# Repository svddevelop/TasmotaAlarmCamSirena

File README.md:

# Tasmota Alarm Camera and Sirena Control

This is a budget control unit that allows connecting a siren and an IPC camera using the DI contact.  
Power supply: 5V – 12V.  
Connection to an external siren with voltage level matching the power supply.  
Camera control connection to the DI signal at 3.3V level.

### Tasmota Configuration

The configuration includes the following elements:

- **Relay1** — enables monitoring of the sensor.  
  Used to activate tracking of the sensor signal (e.g., Reed contact).  
  Can be activated via the device control panel, through the web interface with the request  
  `http://<device_ip>/cm?cmnd=power1%201` (to turn on) and  
  `http://<device_ip>/cm?cmnd=power1%200` (to turn off),  
  or by sending an MQTT message to the topic  
  `cmnd/tasmota_<DeviceID>/POWER1` with payload `ON` or `OFF`.

- **Relay2** — forced siren activation.  
  If a siren is used, its activation can be triggered programmatically via the device control panel,  
  through the web interface with the request  
  `http://<device_ip>/cm?cmnd=power2%201` (to turn on) and  
  `http://<device_ip>/cm?cmnd=power2%200` (to turn off),  
  or by sending an MQTT message to the topic  
  `cmnd/tasmota_<DeviceID>/POWER2` with payload `ON` or `OFF`.  
  If a camera is used, the recording trigger signal will be sent automatically.

- **Switch3** — shows the current state of the sensor.  
  Can be checked via the web interface with the request  
  `http://<device_ip>/cm?cmnd=status%2010`,  
  or through MQTT by sending the message `10` to the topic  
  `cmnd/tasmota_<DeviceID>/Status`.

`<device_ip>` — the unique IP address of the device in your network.  
`<DeviceID>` — the unique identifier of the device.
### Curcuit

[see](circuit/kicad/Esp8266-DomoticzAlarm-2B/README.md)

### Plugin for Domoticz

[see](scripts/Domoticz/plugins/TasmotaMQTTAlarmCtrl/README.md)

---
---

More description you can see at [this site](https://smartthings.cloudns.org/).

[The device installation](https://smartthings.cloudns.org/page/tacs/)

[The case for the device](https://www.thingiverse.com/thing:7336493)

[The case for the reed-contact](https://www.thingiverse.com/thing:7336538)

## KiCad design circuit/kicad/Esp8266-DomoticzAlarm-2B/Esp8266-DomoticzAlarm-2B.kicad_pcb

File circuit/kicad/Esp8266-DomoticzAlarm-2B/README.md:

# Circuit

### Shematic

[Curcuit](Esp8266-DomoticzAlarm-2B.pdf)

### Board

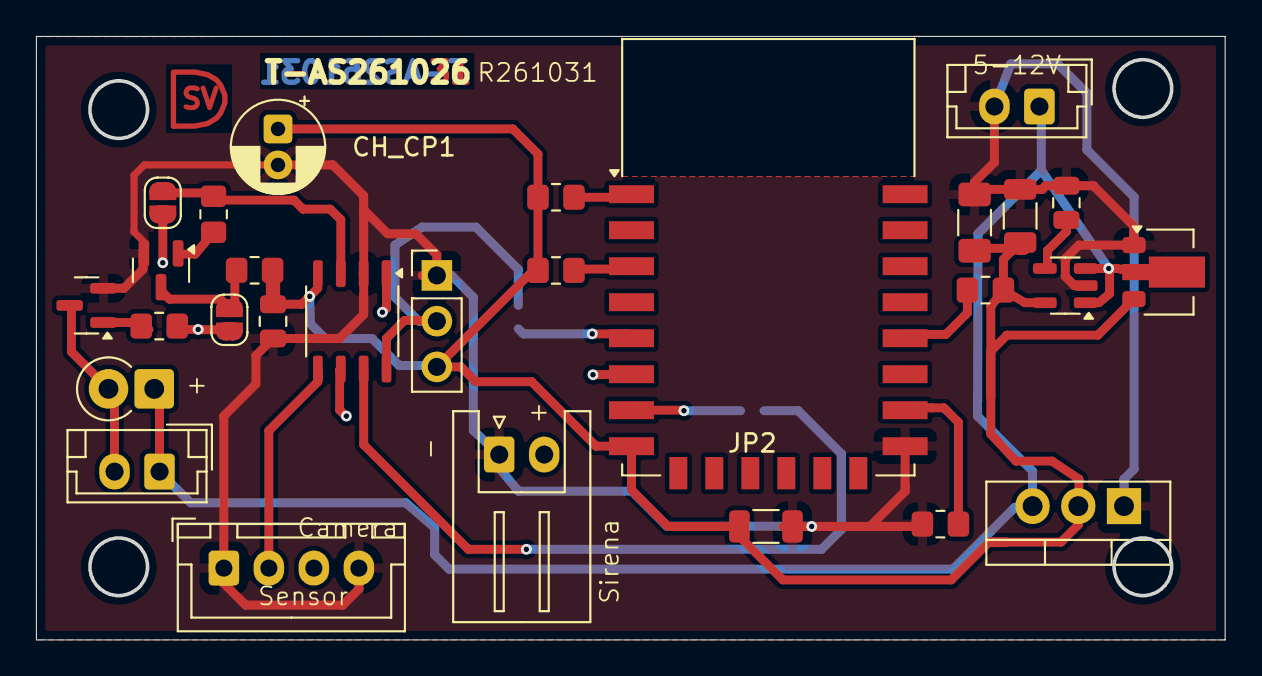
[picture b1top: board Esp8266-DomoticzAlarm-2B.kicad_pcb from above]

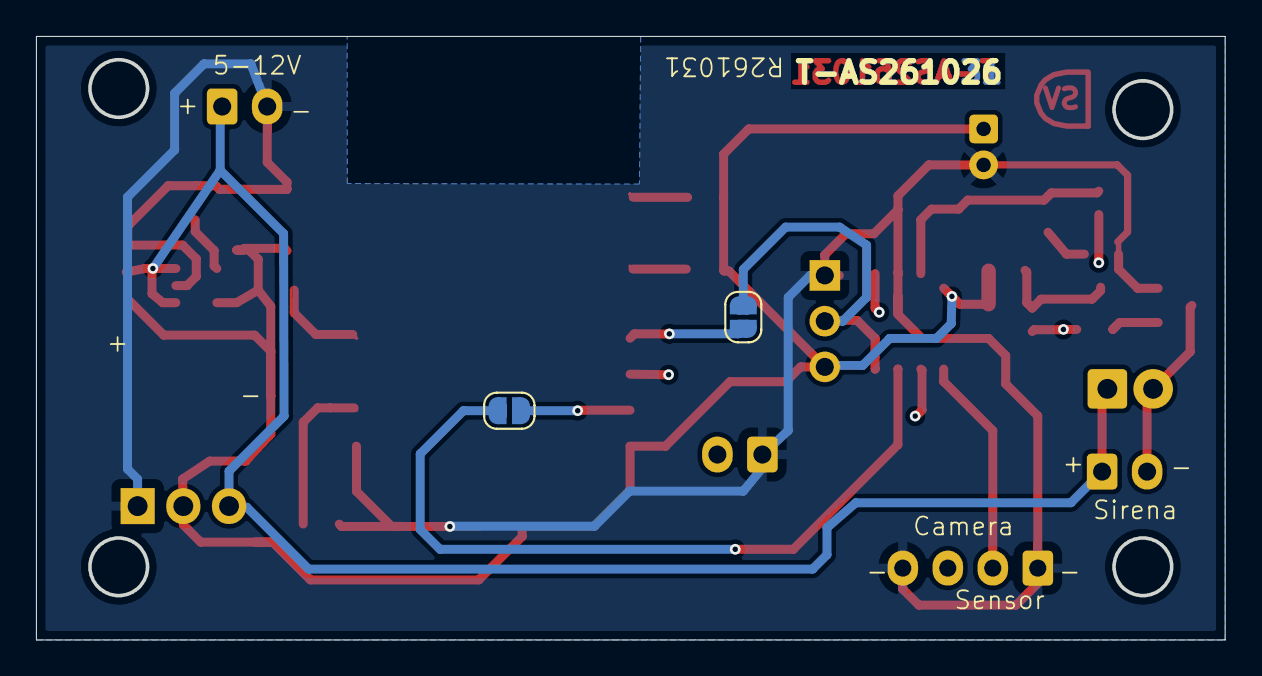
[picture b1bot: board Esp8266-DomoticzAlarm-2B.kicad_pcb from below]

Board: 4 copper layers, 66.0 x 33.5 mm, 30 parts (2 on the bottom side), 21 nets.

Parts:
CH_C1: 100nF; C_0805_2012Metric
CH_C2, CH_C4: 100nF; C_1206_3216Metric
CH_C3: 4,7µF; C_1206_3216Metric_Pad1.33x1.80mm_HandSolder
CH_C5: 470nF; C_0805_2012Metric
CH_CP1: C_Polarized; CP_Radial_D5.0mm_P2.00mm
CH_J7: ALARM_IN; JST_XH_B4B-XH-A_1x04_P2.50mm_Vertical
CH_J8: CH_ALARM_OUT; JST_EH_B2B-EH-A_1x02_P2.50mm_Vertical
CH_J10: CH_12V; JST_EH_B2B-EH-A_1x02_P2.50mm_Vertical
D1: 1N4001; D_DO-41_SOD81_P2.54mm_Vertical_KathodeUp
J2a1: Conn_01x02; JST_XH_S2B-XH-A_1x02_P2.50mm_Horizontal
JP1, JP2, JP3, JP4: Jumper_2_Bridged; SolderJumper-2_P1.3mm_Open_RoundedPad1.0x1.5mm
Q1, Q2: BC817; SOT-23
R1, R8: 100; R_0805_2012Metric_Pad1.20x1.40mm_HandSolder
R2, R3, R4, R5, R10: 10k; R_0805_2012Metric_Pad1.20x1.40mm_HandSolder
U1: CH32V003JxMx; JEITA_SOIC-8_3.9x4.9mm_P1.27mm
U2: ESP-12E
U3: HT7333; SOT-89-3
U4: MIC5219-3.3YM5; SOT-23-5
U5: LD1117V33; TO-220-3_Vertical
ch_J3: CH_PROG; PinHeader_1x03_P2.54mm_Vertical

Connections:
A1-: CH_J8.2, D1.2 (A), Q2.3 (C)
ALARMFROMESP: JP4.1 (A), U2.5 (GPIO14)
ALARM_CAM_DI: CH_J7.3, U1.1 (PD6/PA1)
B1+: CH_J8.1, CH_J10.1, D1.1 (K), U3.2 (VIN), U4.1 (IN), U4.3 (EN), U5.3 (VI)
CH_A2: JP1.1 (A), R8.2, U1.3 (PA2)
CH_ALARM_BREAKE_A: U1.6 (PC2), U2.6 (GPIO12)
CH_ALARM_IN: CH_J7.2, J2a1.2, U1.5 (PC1)
CH_C4: JP2.2 (B), U1.7 (PC4)
CH_D1D4D4: JP4.2 (B), U1.8 (PD1/PD4/PD5), ch_J3.2
CH_GND: CH_C1.2, CH_C2.1, CH_C3.1, CH_C4.2, CH_C5.1, CH_CP1.2, CH_J7.1, CH_J7.4, CH_J10.2, J2a1.1, Q1.2 (E), Q2.2 (E), R3.1, U1.2 (VSS), U2.15 (GND), U3.1 (GND), U4.2 (GND), U5.1 (GND), ch_J3.1
CH_VDD: CH_C1.1, CH_C2.2, CH_C3.2, CH_C4.1, CH_CP1.1, R2.2, R4.2, R5.2, R10.2, U1.4 (VDD), U2.8 (VCC), U3.3 (VOUT), U4.5 (OUT), U5.2 (VO), ch_J3.3
unnamed: JP1.2 (B), JP3.1 (A), R1.2
unnamed: JP3.2 (B), Q1.3 (C), R10.1
unnamed: Q1.1 (B), R8.1
unnamed: Q2.1 (B), R1.1
unnamed: R5.1, U2.3 (EN)
unnamed: R4.1, U2.18 (GPIO0)
unnamed: R3.2, U2.16 (GPIO15)
unnamed: R2.1, U2.1 (~RST)
unnamed: CH_C5.2, U4.4 (BP)
SWITCH_ALARMSTATUS: JP2.1 (A), U2.7 (GPIO13)

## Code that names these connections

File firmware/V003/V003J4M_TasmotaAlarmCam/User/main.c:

//  This µC have 3 inputs signals:
//    PC1 - Alarm Input
//    PC2 - Alarm break (from µC)
//    PC3 - Alarm break (external button)
//
// ... and one output: 
//    PA1 - Alaram output (Piezo-buzzer Sirena)
//
// The external µC set the alarm-signal on "Alarm Input".
// The the alarm doesn't breaked, switched between 2 tones(phases).
// The alarm could be breaked from external µC ("Alarm break (from µC)" must be BREAK_ACTIVE)
//   or from the externam button "Alarm break (external button)" (it must be reise from BREAK_INACTIVE to BREAK_ACTIVE)

//
//  251208-1955 it works
// 

//  251225 - it was changed for tasmota camera1
//

// !!! whan need to append:
//   1) PIN_ALARM_BREAK_B need to change as output for tasmota on pin io14/io3 (type "switch")
//        it could be see the status 


// KiCAD project Z:\WI\pcb\ESP8266\Esp8266-DomoticzAlarm-2\Esp8266-DomoticzAlarm-2A.kicad_pro\Esp8266-DomoticzAlarm-2B

// ===================================================================================
// Libraries, Definitions and Macros
// ===================================================================================
#include "system.h"                               // system functions
#include <gpio.h>                                 // GPIO functions

#include "SYS/millis.h"
//
//        ---------------
//    1 -| PD6       PD5 |- 8
//    2 -| GND       PC4 |- 7
//    3 -| PA2       PC2 |- 6
//    4 -| VCC       PC1 |- 5
//        ---------------
//        ----------------------------------
//    1 -| PIN_ALARM_PS2  WDIO              |- 8
//    2 -| GND            PIN_ALARM_PSL     |- 7
//  * 3 -| PIN_ALARM_PS   PIN_ALARM_BREAK_A |- 6
//    4 -| VCC            PIN_ALARM_INPUT   |- 5 *
//        ----------------------------------
//

//#define PIN_LED   PC0        
#define PIN_WDIO            PD5
#define PIN_ESPALARM        PIN_WDIO  //[I] programmable alarm from ESP. For include these code-snipped need to define #ALARMFROMESP 
#define ALARMFROMESP

#define PIN_ALARM_PS        PA2     // (O)Alarm signal to the Piezo-Buzzer
#define PIN_ALARM_PS2       PD6     // (O)Alarm signal to the Piezo-Buzzer
#define PIN_ALARM_INPUT     PC1     // (I) Alarm input (reed)                     
#define PIN_ALARM_BREAK_A   PC2     // (I) the reaction                          
#define PIN_ALARM_PSL       PC4     // (O) Alarm for ESP

#define BREAK_ACTIVE        (1)
#define BREAK_INACTIVE      (0)

#define ALARM_PULSE_ON      (1)     // the Piezo-buzzer activated
#define ALARM_PULSE_OFF     (0)     // the Piezo-buzzer deactivated

#define ALARM_ON            (1)
#define ALARM_OFF           (0)

#define ALARM_PERIOD_ON     (1000)  // Period in ms, when the Piezo-buzzer is active
#define ALARM_PERIOD_OFF    (500)   // Period in ms, when the Piezo-buzzer is inactive




static struct{

  uint8_t breaked : 1;          //The breaked == BREAK_ACTIVE means that does not need  to do something for alarm
  uint8_t pulse_on: 1;          //When is alarm active, can be swithc between two phases : ALARM_PERIOD_ON and ALARM_PERIOD_OFF
  uint8_t last_break_a: 1;      //It shows that the break active from external µC and does not need to switch alarm
  uint8_t last_break_b: 1;
  uint8_t last_alarm: 1;

} g_status;

#define ALARM_PS(x)         PIN_write(PIN_ALARM_PS, x);PIN_write(PIN_ALARM_PS2, x)


// ===================================================================================
// Main Function
// ===================================================================================
int main(void) {

  STK_init();
  HSI_enable();


  // Setup
  PIN_output(PIN_ALARM_PS);                         // Alarm signal to the Piezo-Buzzer
  PIN_output(PIN_ALARM_PS2);                        // Alarm signal to the Piezo-Buzzer
  PIN_output(PIN_ALARM_PSL);                        // Alarm signal to the ESP
  PIN_write(PIN_ALARM_PS, ALARM_PERIOD_OFF);
  PIN_write(PIN_ALARM_PS2, ALARM_PERIOD_OFF);
  PIN_write(PIN_ALARM_PSL, ALARM_PERIOD_OFF);

  PIN_input_PU(PIN_ALARM_INPUT);                    // Alarm activation on reise from ALARM_OFF to ALARM_ON
  PIN_input(PIN_ALARM_BREAK_A);                  // Stop alarm. It going from µC
  //PIN_input(PIN_ALARM_BREAK_B);                  // With pull-up.  Stop alarm from the external button

  #ifdef ALARMFROMESP
  PIN_input_PU(PIN_ESPALARM);
  #endif


  
  //ALARM_PS(ALARM_PULSE_OFF);   
  PIN_write(PIN_ALARM_PS, ALARM_PULSE_OFF);
  PIN_write(PIN_ALARM_PS2, ALARM_PULSE_OFF);             

  g_status.breaked    =   BREAK_INACTIVE;
  g_status.pulse_on   =   ALARM_PULSE_ON;
  g_status.last_alarm =   ALARM_OFF;

  // Loop
  while(1) {

    uint8_t pin;



    //
    pin = PIN_read(PIN_ALARM_INPUT);
    PIN_write(PIN_ALARM_PSL, pin); 
    if ((pin == ALARM_ON) & (g_status.last_alarm == ALARM_OFF))
        g_status.last_alarm = ALARM_ON;

    //if (pin == ALARM_OFF)
    //    g_status.last_alarm = ALARM_OFF;

    //*/    

    //
    pin = PIN_read(PIN_ALARM_BREAK_A);

    if (( pin == BREAK_ACTIVE) )//& ( g_status.last_break_a == BREAK_INACTIVE))
    {

      g_status.breaked = BREAK_ACTIVE; 
      g_status.last_break_b = BREAK_INACTIVE;
    }
    else 
      g_status.breaked = BREAK_INACTIVE;

    g_status.last_break_a = pin;
    //*/


    // check for the break from the stop-alarm button
    pin = BREAK_INACTIVE;
    g_status.last_break_b = pin;
    //*
    #ifdef ALARMFROMESP
    pin = PIN_read(PIN_ESPALARM);
    if (( pin == ALARM_ON))// & ( g_status.last_break_b == BREAK_INACTIVE))  
    {
      g_status.breaked    = BREAK_INACTIVE; 
      g_status.last_alarm = ALARM_ON;
    }
    //g_status.last_break_b = pin;
    #endif
    //*/

    // switch alarm to OFF if any break is active
    if (g_status.breaked == BREAK_ACTIVE){

        //ALARM_PS(ALARM_PULSE_OFF);
        PIN_write(PIN_ALARM_PS, ALARM_PULSE_OFF);
        PIN_write(PIN_ALARM_PS2, ALARM_PULSE_OFF);             
        //PIN_write(PIN_ALARM_PSL, ALARM_PULSE_OFF);             
        g_status.last_alarm = ALARM_OFF;
    }
    //*/

    

    //
    //pin = ALARM_ON;
    //g_status.last_alarm = ALARM_OFF;

    if (g_status.last_alarm == ALARM_ON) {  

                   
      if (g_status.breaked == BREAK_INACTIVE){

        if (g_status.pulse_on == ALARM_PULSE_ON){

          //ALARM_PS(ALARM_PULSE_ON);
          PIN_write(PIN_ALARM_PS, ALARM_PULSE_ON);
          PIN_write(PIN_ALARM_PS2, ALARM_PULSE_ON);             
          g_status.pulse_on = ALARM_PULSE_OFF;
          DLY_ms(ALARM_PERIOD_ON);

        }
        else { //if (g_status.pulse_on == ALARM_PULSE_ON)

          //ALARM_PS(ALARM_PULSE_OFF);
          PIN_write(PIN_ALARM_PS, ALARM_PULSE_OFF);
          PIN_write(PIN_ALARM_PS2, ALARM_PULSE_OFF);             
          g_status.pulse_on = ALARM_PULSE_ON;
          DLY_ms(ALARM_PERIOD_OFF);

        }//if (g_status.pulse_on == ALARM_PULSE_ON)
        

      }//if (g_status.breaked == BREAK_ACTIVE)

    }//if ( pin == 1)
    //g_status.last_alarm = pin;
    //*

    //DLY_ms(400);                                  // wait a bit

  }//while(1)
}

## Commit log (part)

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2026-01-01 image in README.md
2026-01-01 image in README.md 2
2026-01-12 Domoticz plugin
2026-01-12 KiCAD picture connections circuit
2026-01-13 circuit: power over HT7333. PDF. READ.md
2026-01-15 readme in circuit
2026-02-07 ver 1.2.0
2026-02-07 main readme
2026-02-10 little changes in PCB
2026-03-28 changes in README.md
2026-04-16 changes 20260416
